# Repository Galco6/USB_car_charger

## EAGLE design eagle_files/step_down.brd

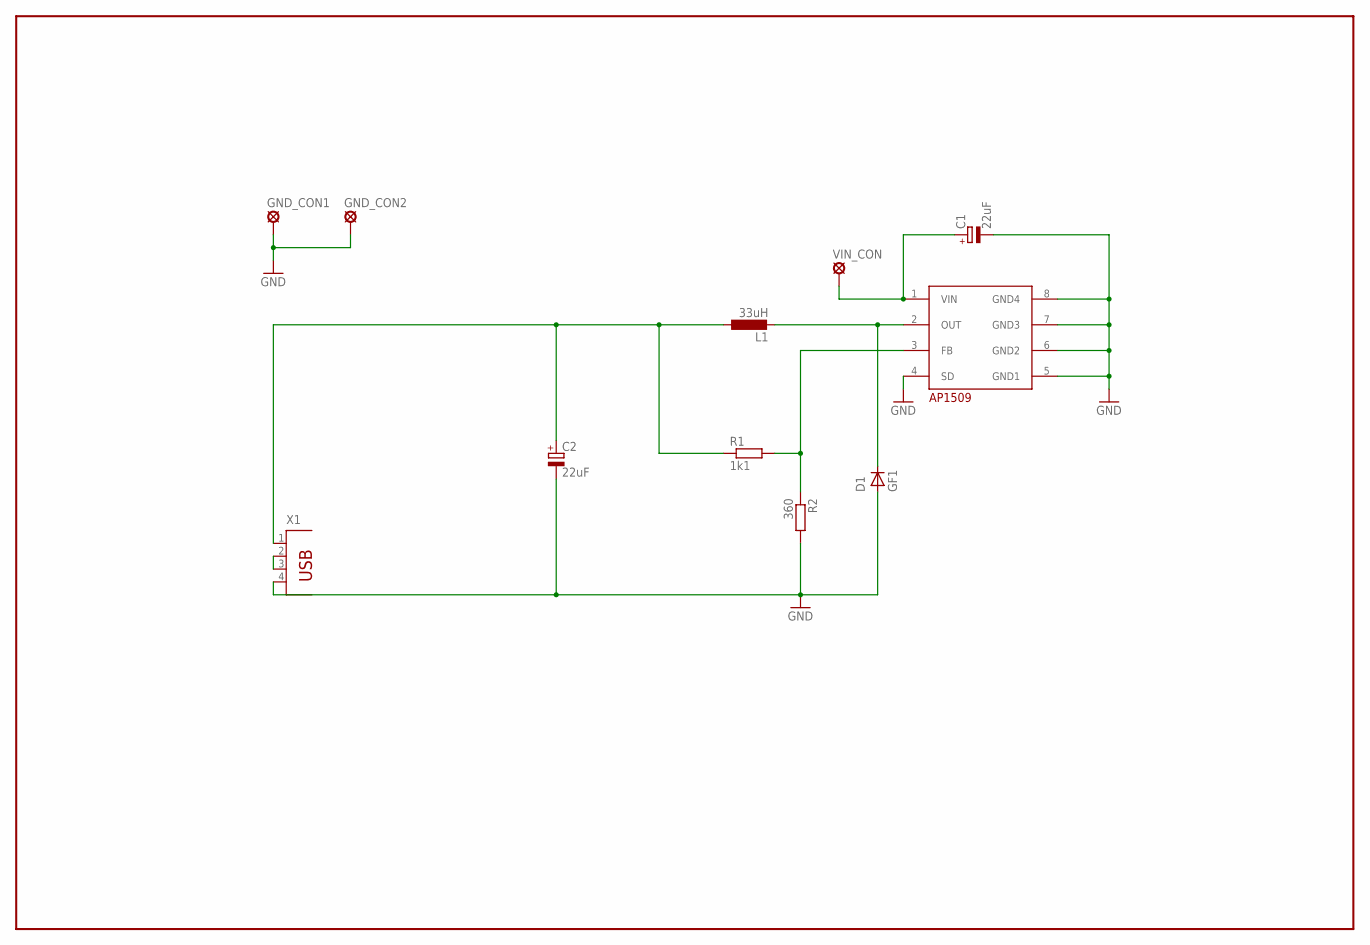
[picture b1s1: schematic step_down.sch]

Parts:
C1: 22uF; CT7343
C2: 22uF; CT3216
D1: GF1; SMA-DO214AC
GND_CON1, GND_CON2: SE14
L1: 33uH; L8051
R1: 1k1; M3216
R2: 360; M3216
U1: AP1509S; SOIC8
VIN_CON: SE14
X1: PN87520

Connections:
GND: C1.-, C2.-, D1.A, GND_CON1.MP, GND_CON2.MP, R2.2, U1.4 (SD), U1.5 (GND1), U1.6 (GND2), U1.7 (GND3), U1.8 (GND4), X1.4
unnamed: C1.+, U1.1 (VIN), VIN_CON.MP
unnamed: X1.2, X1.3
unnamed: D1.K (C), L1.2, U1.2 (OUT)
unnamed: C2.+, L1.1, R1.1, X1.1
unnamed: R1.2, R2.1, U1.3 (FB)

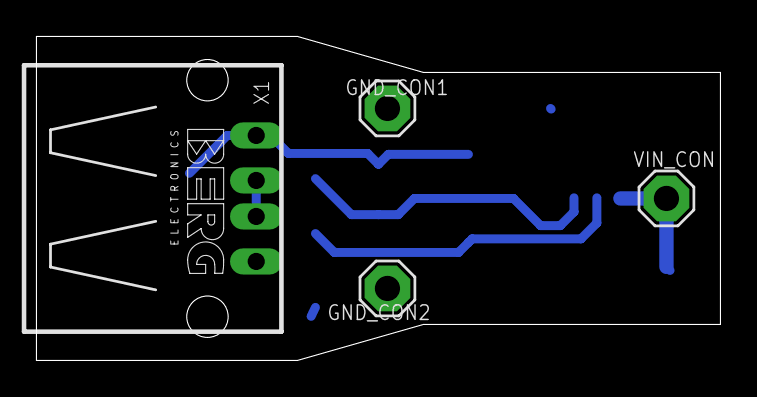
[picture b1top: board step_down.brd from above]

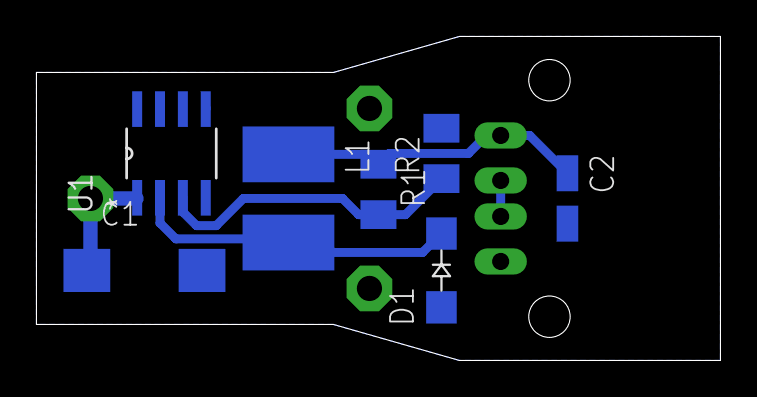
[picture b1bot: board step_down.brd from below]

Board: 2 copper layers, 38.0 x 18.0 mm, 12 parts (8 on the bottom side), 6 nets.

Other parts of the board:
U$1: LOGO6AA_MPEQ_REF

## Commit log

2018-06-06 Eagle files
